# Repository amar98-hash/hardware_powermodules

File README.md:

# hardware_powermodules_ first attempt towards regulators in kicad

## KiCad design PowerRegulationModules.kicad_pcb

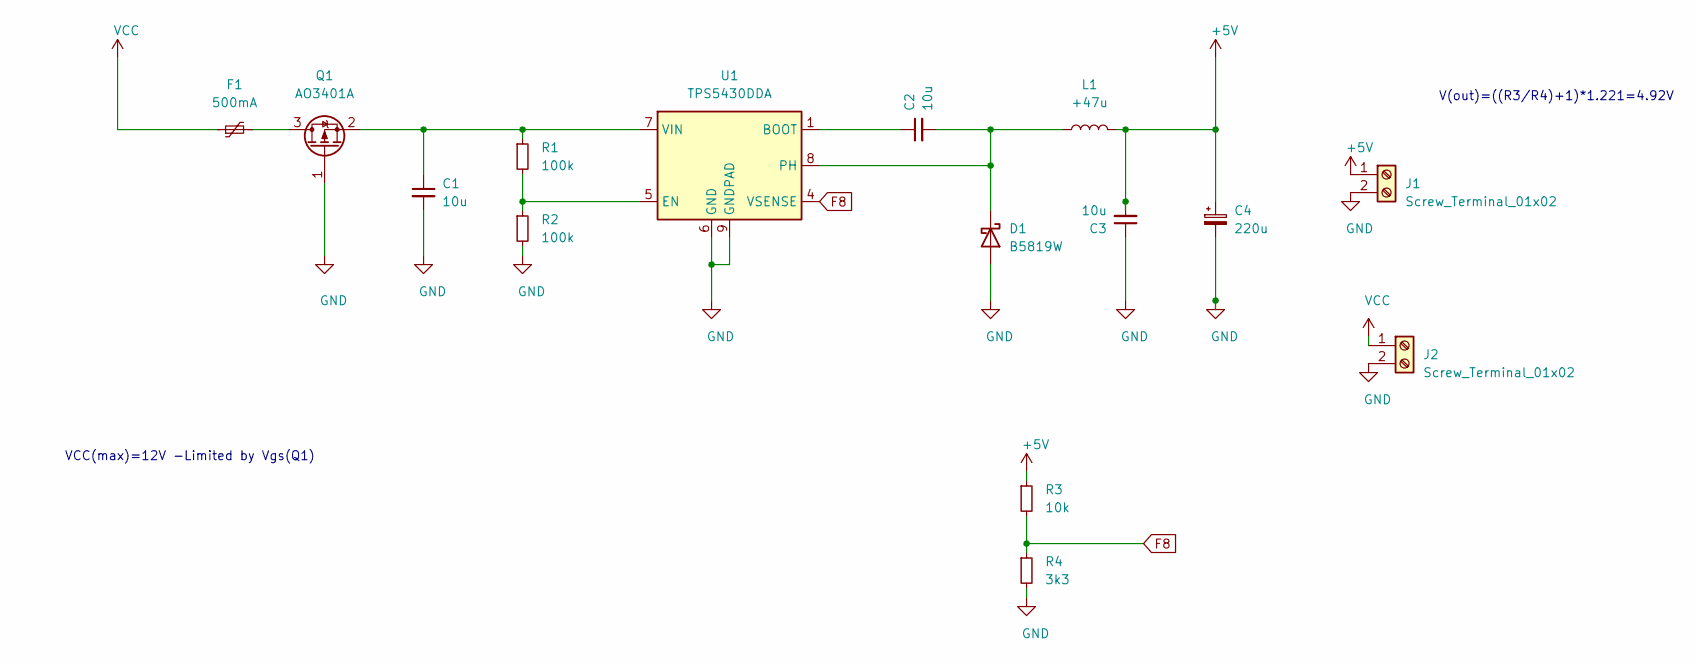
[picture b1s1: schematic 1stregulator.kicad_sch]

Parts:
C1, C2, C3: 10u; C_1206_3216Metric_Pad1.33x1.80mm_HandSolder
C4: 220u; CP_EIA-7343-15_Kemet-W_Pad2.25x2.55mm_HandSolder
D1: B5819W; D_SOD-323F
F1: 500mA; Fuse_1210_3225Metric_Pad1.42x2.65mm_HandSolder
J1, J2: Screw_Terminal_01x02; TerminalBlock_Altech_AK300-2_P5.00mm
L1: +47u; L_12x12mm_H8mm
Q1: AO3401A; SC-59_Handsoldering
R1, R2: 100k; R_0805_2012Metric_Pad1.20x1.40mm_HandSolder
R3: 10k; R_0805_2012Metric_Pad1.20x1.40mm_HandSolder
R4: 3k3; R_0805_2012Metric_Pad1.20x1.40mm_HandSolder
U1: TPS5430DDA; TI_SO-PowerPAD-8_ThermalVias

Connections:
+5V: C3.2, C4.1, J1.1, L1.2, R3.1
F8: R3.2, R4.1, U1.4 (VSENSE)
GND: C1.2, C3.1, C4.2, D1.2 (A), J1.2, J2.2, Q1.1 (G), R2.2, R4.2, U1.6 (GND), U1.9 (GNDPAD)
unnamed: C1.1, Q1.2 (S), R1.1, U1.7 (VIN)
unnamed: C2.1, U1.1 (BOOT)
unnamed: C2.2, D1.1 (K), L1.1, U1.8 (PH)
unnamed: F1.2, Q1.3 (D)
unnamed: R1.2, R2.1, U1.5 (EN)
VCC: F1.1, J2.1

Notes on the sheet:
VCC(max)=12V -Limited by Vgs(Q1)
V(out)=((R3/R4)+1)*1.221=4.92V

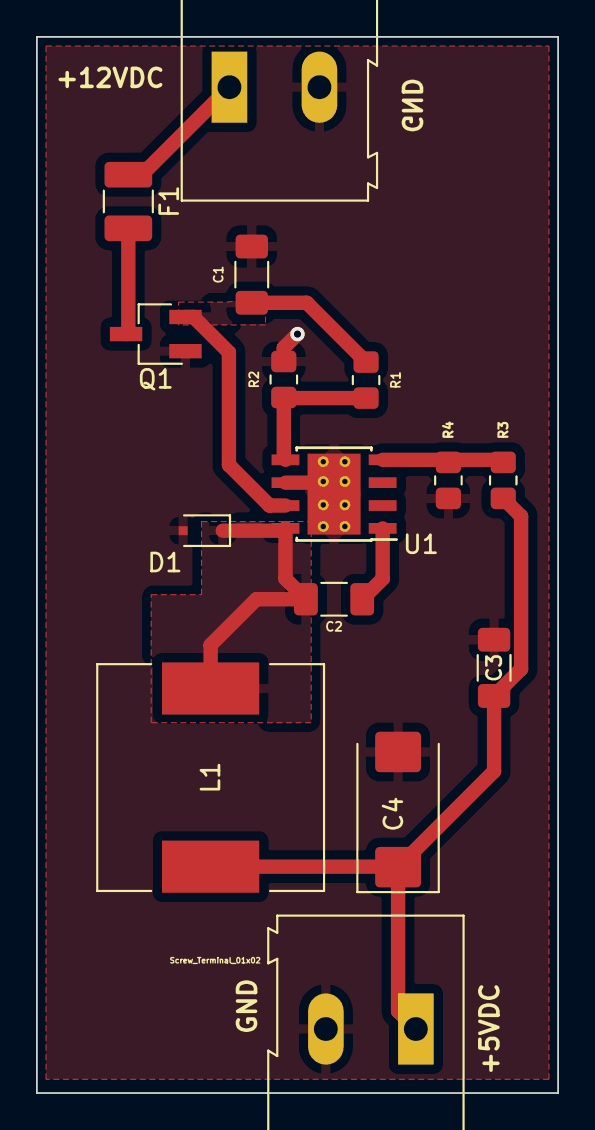
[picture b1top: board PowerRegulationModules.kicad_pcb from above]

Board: 2 copper layers, 29.0 x 58.7 mm, 15 parts (0 on the bottom side), 9 nets.

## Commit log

2021-07-18 DRC passed first 5VDC regulator
